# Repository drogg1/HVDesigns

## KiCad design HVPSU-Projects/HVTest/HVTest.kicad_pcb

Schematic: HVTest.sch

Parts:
J6, J7, J8: AWG_14_Hole; MountingHole_3.5mm_Pad

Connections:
GND: J6.1, J7.1, J8.1; also elsewhere on the board

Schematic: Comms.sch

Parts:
C1: 1u; R_0603
C2: 1u; C_0603
C3, C20: 0.1u; C_0402
D1, D2: LED; LED_0805
J1: USB-MICRO-B; USB-uB-Molex-1050170001-V2
P19: CONN_01X02; Pin_Header_Straight_SMT_02x01D
R1, R2: 1k; R_0805
R57: 1M; R_0402
U1: NUF2101MT1G; TSOP-6
U2: FT230X; QFN-16-1EP_4x4mm_Pitch0.65mm
Z1, Z2: MI0805K400R-10; L0805

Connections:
+5V: C2.1, C3.1, U2.10, Z2.1; also elsewhere on the board
/Comms/RXD: P19.2, U2.2; also elsewhere on the board
/Comms/TXD: P19.1, U2.15; also elsewhere on the board
/Comms/VCCIO: C1.1, R1.1, R2.1, U2.1, U2.8, U2.9
GND: C1.2, C2.2, C3.2, C20.2, R57.2, U2.3, U2.13, U2.17, Z1.1; also elsewhere on the board
GNDPWR: C20.1, J1.6, R57.1
unnamed: D1.1, U2.11
unnamed: D1.2, R1.2
unnamed: D2.1, U2.5
unnamed: D2.2, R2.2
unnamed: J1.1, U1.5, Z2.2
unnamed: J1.2, U1.4
unnamed: J1.3, U1.6
unnamed: J1.5, U1.2, Z1.2
unnamed: U1.1, U2.6
unnamed: U1.3, U2.7

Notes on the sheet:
VCCIO can supply a maximum of 50 mA.

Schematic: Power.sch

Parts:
BT1: Battery; KEY1027-ND
C6, C7: 1uF; C_0603
P1: CONN_01X02; Pin_Header_Straight_SMT_02x01D
P2, P3, P4: CONN_01X03; Pin_Header_Straight_1x03
P5, P6, P7: CONN_01X01; Pin_Header_Straight_1x01
S1: SPDT; PCM12SMTR
U4: MCP1700t-3302E/TT; SOT23

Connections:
+3V3: C7.1, P5.1, P6.1, P7.1, U4.3; also elsewhere on the board
+5V: C6.1, U4.2; also elsewhere on the board
GND: BT1.2, C6.2, C7.2, U4.1; also elsewhere on the board
unnamed: BT1.1, S1.2
unnamed: P1.2, S1.1
VBATT: P1.1, P2.1, P3.1, P4.1; also elsewhere on the board
VDAC: P2.3, P3.3, P4.3; also elsewhere on the board
VIC: P3.2; also elsewhere on the board
VREFDAC: P2.2; also elsewhere on the board
VSW: P4.2; also elsewhere on the board

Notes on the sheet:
Reference DAC Supply
Switch IC Supply
CW Chain Supply
250 mA LDO

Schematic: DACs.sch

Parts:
C8, C9: 0.1uF; C_0402
C81: 1uF; C_0603
U5: MAX5531; TQFN-12-1EP_4x4mm_Pitch0.8mmV2
U6: MCP4912; TSSOP-14_4.4x5mm_Pitch0.65mm
W1: TEST_1P; Measurement_Point_Round-SMD-Pad_Small

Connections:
+3V3: C8.1, U6.1, U6.9, U6.13; also elsewhere on the board
/CheetahSocket/MSPSCLK: U5.2, U6.4; also elsewhere on the board
/DACs/MOSI: U5.3, U6.5; also elsewhere on the board
/DACs/~REFCSN: U5.1; also elsewhere on the board
/DACs/~SUPPCSN: U6.3; also elsewhere on the board
DACO: U5.10, U5.12; also elsewhere on the board
GND: C8.2, C9.2, C81.2, U5.9, U5.EP, U6.8, U6.12; also elsewhere on the board
unnamed: U5.4, W1.1
VDAC: C81.1, U6.10; also elsewhere on the board
VHIGH: U6.14; also elsewhere on the board
VIC: U6.11; also elsewhere on the board
VREFDAC: C9.1, U5.8; also elsewhere on the board

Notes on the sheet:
ULP Reference DAC
Dual DAC to generate supply voltage as well as comparator high threshold
Selectable supply
3.3 V Supply current 0.25 mA (MCP4912)
Supply current 6 uA (MAX5531)

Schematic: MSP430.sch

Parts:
C4: 1uF; C_0603
C5, C80: 0.1uF; C_0402
D3: LED; LED_0805
P20: CONN_01X04; Pin_Header_Straight_SMT_04x01T
R3: 1k; R_0402
R13, R38: 4.7k; R_0402
R39: 1M; R_0402
R58, R59: 10k; R_0402
U3: MSP430G2XX3; TSSOP-28_4.4x9.7mm_Pitch0.65mm

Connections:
+3V3: C4.1, C5.1, P20.1, R13.2, R38.2, R39.1, R58.2, R59.2, U3.1; also elsewhere on the board
/CheetahSocket/MSPSCLK: U3.11; also elsewhere on the board
/CheetahSocket/~ICCSN: U3.13; also elsewhere on the board
/Comms/RXD: U3.4; also elsewhere on the board
/Comms/TXD: U3.3; also elsewhere on the board
/DACs/MOSI: U3.12; also elsewhere on the board
/DACs/~REFCSN: R59.1, U3.17; also elsewhere on the board
/DACs/~SUPPCSN: R58.1, U3.16; also elsewhere on the board
/HVMeasurement/SCL: R38.1, U3.22; also elsewhere on the board
/HVMeasurement/SDA: R13.1, U3.23; also elsewhere on the board
/MSP430/INTS0: U3.21; also elsewhere on the board
/MSP430/INTS1: U3.20; also elsewhere on the board
/MSP430/PWS0: U3.18; also elsewhere on the board
/MSP430/PWS1: U3.19; also elsewhere on the board
GND: C4.2, C5.2, C80.2, D3.1, P20.4, U3.28; also elsewhere on the board
LSB: U3.2; also elsewhere on the board
MSB: U3.5; also elsewhere on the board
unnamed: D3.2, R3.2
unnamed: P20.2, U3.25
unnamed: P20.3, R39.2, U3.24
unnamed: R3.1, U3.10
RSTIC: U3.15; also elsewhere on the board
SWCurr: C80.1, U3.6; also elsewhere on the board
VBATT: U3.7; also elsewhere on the board

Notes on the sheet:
Powered by 3V3 Regulator
Smoothing cap potenitally optional
Programming Header

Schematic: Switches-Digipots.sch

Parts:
C12, C17: 1nF; C_0402
C13: 3.3nF; C_0402
C14: 470pF; C_0402
C15, C16, C22: 0.1uF; C_0402
C18, C19: 220pF; C_0402
P9, P10, P11, P12: CONN_01X02; Pin_Header_Straight_SMT_02x01D
U8, U9: MAX4704; QFN-12-1EP_3x3mm_Pitch0.5mm
U10: MCP4651T; QFN-16-4x4

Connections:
+3V3: C15.1, C16.1, C22.1, U8.1, U9.1, U10.13, U10.14, U10.15, U10.16; also elsewhere on the board
/HVMeasurement/SCL: U10.1; also elsewhere on the board
/HVMeasurement/SDA: U10.2; also elsewhere on the board
/MSP430/INTS0: U9.10; also elsewhere on the board
/MSP430/INTS1: U9.9; also elsewhere on the board
/MSP430/PWS0: U8.10; also elsewhere on the board
/MSP430/PWS1: U8.9; also elsewhere on the board
/Switches-Digipots/INO0: C13.1, P10.2, U9.11
/Switches-Digipots/INO1: C17.1, U9.5
/Switches-Digipots/INO2: C19.1, U9.3
/Switches-Digipots/PNO0: C12.1, P9.2, U8.11
/Switches-Digipots/PNO1: C14.1, U8.5
/Switches-Digipots/PNO2: C18.1, U8.3
CIN: C12.2, C14.2, C18.2; also elsewhere on the board
GND: C15.2, C16.2, C22.2, U8.6, U8.7, U8.13, U9.6, U9.7, U9.13, U10.3, U10.4, U10.17; also elsewhere on the board
ICAP1: C13.2, C17.2, C19.2; also elsewhere on the board
ICAP2: P10.1, U9.12; also elsewhere on the board
P0W: P12.1, U10.9; also elsewhere on the board
P1W: P11.1, U10.6; also elsewhere on the board
RIN: P9.1, P12.2, U8.12, U10.10; also elsewhere on the board
SWITCH: P11.2, U10.5; also elsewhere on the board

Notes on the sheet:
Dual digipot for setting pulse width and delay resistances
Analog switch to select integration capacitor
Analog switch to select pulse width timing cap
Switch Bypass
Digipot Bypasses
I2C Address "0101A2A1A0" "0101111" <- Configured As
3.3 V Supply current 0.25 mA (MCP461T) 1 uA (MAX4704)

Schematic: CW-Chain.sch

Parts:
C23: 100uF; Tantalum_Case-C_EIA-6032-28_Reflow
C24, C30, C31, C33, C34, C38, C39, C41, C42, C46, C47, C49, C50, C54, C55, C57, C58, C62, C63, C65, C66, C70, C71, C73, C74: 0.1uF; C_1812
C25: 33pF; C_0402
C26: 3nF; C_0402
C27, C28, C29, C32, C35, C36, C37, C40, C43, C44, C45, C48, C51, C52, C53, C56, C59, C60, C61, C64, C67, C68, C69, C72: 0.1uF; C_1210
D4, D5, D6, D7, D8, D9, D10, D11, D12, D13, D14, D15: MMBD3004S; SOT23
GND1: CONN_01X01; Pin_Header_Straight_1x01
J2: SMA; SMA-EDGE
J3: UFL-CONN; U.FL-R-SMT
J4: RF_SHIELD_TWO_PIECES; BMI-S-230-F-R
OUT1: TEST_1P; Measurement_Point_Round-SMD-Pad_Small
P13: CONN_01X02; Pin_Header_Straight_SMT_02x01D
P17: CONN_01X01; Pin_Header_Straight_1x01
Q1: NMOS-DMG3420U; SOT23
R12: 5.1; R_0603
R14, R15: 1M; R_0402
R16, R17, R19, R20, R21, R22, R25, R26: 0; R_1206
R18, R23, R24, R27, R28, R29, R30, R31, R32, R33, R34, R35: 1M; R_0805
R36: 1G; R_2512
R37: 2M; R_0805
R52, R53: 0; R_0805
ST1, ST2, ST3, ST4, ST5, ST6, ST7, ST8, ST9, ST10, ST11, ST12: CONN_01X01; Pin_Header_Straight_1x01
U14: MAX9634; TSOT-23-5

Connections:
/CW-Chain/S1: C28.1, C30.1, C32.2, D4.3, D5.1, R16.1, R18.1, R19.2
/CW-Chain/S2: C32.1, C33.2, C36.2, D5.3, D6.1, R19.1, R21.2, R23.1
/CW-Chain/S3: C36.1, C38.1, C40.2, D6.3, D7.1, R21.1, R24.1, R25.2
/CW-Chain/S4: C40.1, C41.2, C44.2, D7.3, D8.1, R25.1, R27.1
GND: C23.2, C25.2, C28.2, C30.2, C31.2, C33.1, C34.1, C38.2, C39.2, C41.1, C42.1, C46.2, C47.2, C49.1, C50.1, C54.2, C55.2, C57.1, C58.1, C62.2, C63.2, C65.1, C66.1, C70.2, C71.2, C73.1, C74.1, D4.1, GND1.1, J2.2, J2.3, J2.4, J2.5, J3.2, J3.3, J4.1, Q1.3, R14.2, R15.2, R16.2, U14.1, U14.2; also elsewhere on the board
HVR: R36.2; also elsewhere on the board
unnamed 42: C23.1, R12.2, U14.4; also elsewhere on the board
unnamed: C24.2, C25.1, C26.1, OUT1.1, R15.1
unnamed: C26.2, J2.1, J3.1
unnamed 45: C27.1, R17.2; also elsewhere on the board
unnamed: C27.2, C29.1, D4.2, R17.1, R20.2
unnamed: C29.2, C35.1, D5.2, R20.1, R22.2
unnamed: C31.1, R18.2, ST1.1
unnamed: C34.2, R23.2, ST2.1
unnamed: C35.2, C37.1, D6.2, R22.1, R26.2
unnamed: C37.2, C43.1, D7.2, R26.1
unnamed: C39.1, R24.2, ST3.1
unnamed: C42.2, R27.2, ST4.1
unnamed: C43.2, C45.1, D8.2
unnamed: C44.1, C46.1, C48.2, D8.3, D9.1, R28.1
unnamed: C45.2, C51.1, D9.2
unnamed: C47.1, R28.2, ST5.1
unnamed: C48.1, C49.2, C52.2, D9.3, D10.1, R29.1
unnamed: C50.2, R29.2, ST6.1
unnamed: C51.2, C53.1, D10.2
unnamed: C52.1, C54.1, C56.2, D10.3, D11.1, R30.1
unnamed: C53.2, C59.1, D11.2
unnamed: C55.1, R30.2, ST7.1
unnamed: C56.1, C57.2, C60.2, D11.3, D12.1, R31.1
unnamed: C58.2, R31.2, ST8.1
unnamed: C59.2, C61.1, D12.2
unnamed: C60.1, C62.1, C64.2, D12.3, D13.1, R32.1
unnamed: C61.2, C67.1, D13.2
unnamed: C63.1, R32.2, ST9.1
unnamed: C64.1, C65.2, C68.2, D13.3, D14.1, R33.1
unnamed: C66.2, R33.2, ST10.1
unnamed: C67.2, C69.1, D14.2
unnamed: C68.1, C70.1, C72.2, D14.3, D15.1, R34.1
unnamed: C69.2, D15.2
unnamed: C71.1, R34.2, ST11.1
unnamed: C72.1, C73.2, D15.3, R35.1, R52.2
unnamed: C74.2, P17.1, R35.2, R37.2, R53.2
unnamed: P13.1, Q1.1, R14.1
unnamed 119: Q1.2; also elsewhere on the board
unnamed: R36.1, R52.1, R53.1
ST12: C24.1, R37.1, ST12.1
SWCurr: U14.3; also elsewhere on the board
SWDLY: P13.2; also elsewhere on the board
VSW: R12.1, U14.5; also elsewhere on the board

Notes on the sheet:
Populate to short out lower stages
Current Sense Amp
Optional
Feedback Res
Output

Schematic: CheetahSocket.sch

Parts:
J5: HIROSE-DF12; CheetahSocket
P14: CONN_01X03; Pin_Header_Straight_1x03_Pitch2.54mm
P23, P24: CONN_01X01; Pin_Header_Straight_1x01
P25: CONN_01X02; Pin_Header_Straight_1x02_Pitch2.54mm
R40, R41, R42: 10k; R_0402
R43, R44, R45: 1k; R_0402
U11: TLP293-4; SO-16-N

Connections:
+3V3: P25.1; also elsewhere on the board
/CheetahSocket/MSPSCLK: J5.17, P14.3, U11.1; also elsewhere on the board
/CheetahSocket/SPI1_SSa: R40.2, U11.12; also elsewhere on the board
/CheetahSocket/~ICCSN: J5.21, P14.1, U11.5; also elsewhere on the board
/DACs/MOSI: J5.19, P14.2, U11.3; also elsewhere on the board
/SwitchIC/MOSI: R41.2, U11.14; also elsewhere on the board
/SwitchIC/SCLK: R42.2, U11.16; also elsewhere on the board
GND: J5.2, J5.4, J5.6, P23.1, P24.1, R43.2, R44.2, R45.2, U11.11, U11.13, U11.15; also elsewhere on the board
unnamed: J5.1, J5.3, J5.5, P25.2
unnamed: R43.1, U11.6
unnamed: R44.1, U11.4
unnamed: R45.1, U11.2
VIC: R40.1, R41.1, R42.1; also elsewhere on the board

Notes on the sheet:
Opto-isolation
Potential connection to GPIO
Connector to MCA10 Optional connections to 3.3V supply
Currently outputs are buffered to decrease rise time to enable consistent SPI communication

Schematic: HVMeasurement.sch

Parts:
C75, C78, C79: 0.1uF; R_0402
C76, C77: 1uF; R_0603
P15: CONN_01X02; Pin_Header_Straight_SMT_02x01D
P18: CONN_01X01; Pin_Header_Straight_1x01
R48: 10M; R_0402
R49: 10k; R_0402
R50: 220k; R_0402
R51: 1k; R_0402
U12: LTC2050; TSOT-23-5
U13: LTC2451; DFN-8-1EP_2x3mm_Pitch0.5mm

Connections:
+3V3: C75.1, C76.1, C77.1, C79.1, U12.5, U13.3, U13.4; also elsewhere on the board
/HVMeasurement/SCL: U13.7; also elsewhere on the board
/HVMeasurement/SDA: U13.8; also elsewhere on the board
GND: C75.2, C76.2, C77.2, C78.2, C79.2, P15.2, R48.2, R49.1, U12.2, U13.1, U13.2, U13.5, U13.9; also elsewhere on the board
unnamed: C78.1, P15.1, R51.1, U13.6
unnamed: P18.1, R48.1, U12.3
unnamed: R49.2, R50.2, U12.4
unnamed: R50.1, R51.2, U12.1

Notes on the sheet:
128 mV @ 1206V worse case 1% tolerances
Av = 23 => 23*128 mV = 2.944 FS
12.7 nA @ 1206 V = 15.3 uW 6.3 nA @ 600 V = 3.78 uW worse case 1% tolerances
I2C Address "0010100"
3.3 V supply current 0.8 mA (LTC2050) 0.4 mA (LTC2451)
Connect 100G Res
Allows measurement of final HV stage with minimal loading (1000V/100Gohm = 10 nA => 10 uW)

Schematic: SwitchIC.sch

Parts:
C10, C11, C21: 1uF; C_0603
P8: CONN_01X02; Pin_Header_Straight_SMT_02x01V
P16, P22: CONN_01X02; Pin_Header_Straight_1x02_Pitch2.54mm
P21: CONN_01X03; Pin_Header_Straight_SMT_03x01STAGGERED
R4, R5: 10; R_0402
R6, R7, R8, R10, R11, R56: 1M; R_0402
R9: 33M; R_0402
R54: 560k; R_0402
R55: 2M; R_0402
RST1: TEST_1P; Pin_Header_Straight_SMT_01x01
RV1, RV2: 20k; EVM3Y-POT
RV3: 1M; EVM3Y-POT
U7: switch_ic4/5; test_socket

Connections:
/CheetahSocket/SPI1_SSa: U7.20; also elsewhere on the board
/SwitchIC/MOSI: U7.19; also elsewhere on the board
/SwitchIC/SCLK: U7.18; also elsewhere on the board
/SwitchIC/VDD: C11.1, R4.2, RV2.3, U7.15
/SwitchIC/VDDA: C10.1, R5.2, U7.11
CIN: U7.17; also elsewhere on the board
DACO: P8.2; also elsewhere on the board
GND: C10.2, C11.2, C21.2, R55.2, R56.1, U7.1, U7.12; also elsewhere on the board
HVR: P22.2, R6.2, R7.1, U7.3; also elsewhere on the board
ICAP1: U7.7; also elsewhere on the board
ICAP2: U7.8; also elsewhere on the board
LSB: P16.1, R9.1, U7.9; also elsewhere on the board
MSB: P16.2, R10.1, U7.10; also elsewhere on the board
unnamed: C21.1, P21.2, U7.2
unnamed: P8.1, R6.1
unnamed: P21.3, RV3.2
unnamed: P22.1, R9.2, R10.2
unnamed: R7.2, R8.2, U7.4
unnamed: R8.1, R11.1, U7.6
unnamed: R11.2, U7.5
unnamed: R54.2, RV3.1
unnamed: R55.1, RV3.3
P0W: RV2.2; also elsewhere on the board
P1W: RV1.2; also elsewhere on the board
RIN: U7.14; also elsewhere on the board
RSTIC: R56.2, RST1.1, U7.13; also elsewhere on the board
SWDLY: RV1.3; also elsewhere on the board
SWITCH: U7.16; also elsewhere on the board
VHIGH: P21.1; also elsewhere on the board
VIC: R4.1, R5.1, R54.1; also elsewhere on the board

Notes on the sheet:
Connects to 50k digipot Channel 0
Connects to array of switchable capacitors
Connects to 50k digipot Channel 1
Set reference current Iset = VDAC / R VsetHIGH = Iset * RFB = Iset * 1e9
ULP Ref DAC
Comparator High Threshold
Limits set point to ensure internal FETs stay in saturation
Sets R that, along with capacitor connected to CIN, sets pulse width of switching pulse
Controls rise and fall time of switch pulse

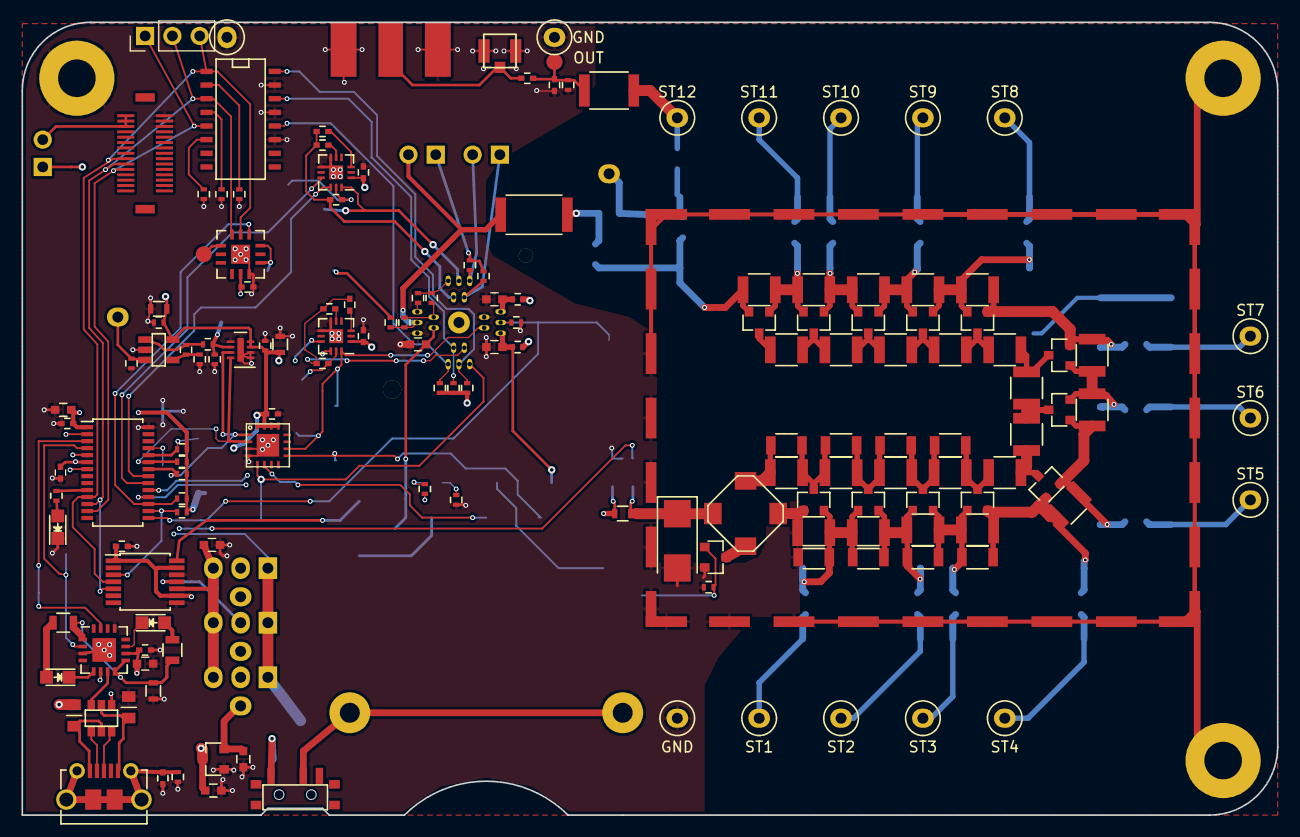
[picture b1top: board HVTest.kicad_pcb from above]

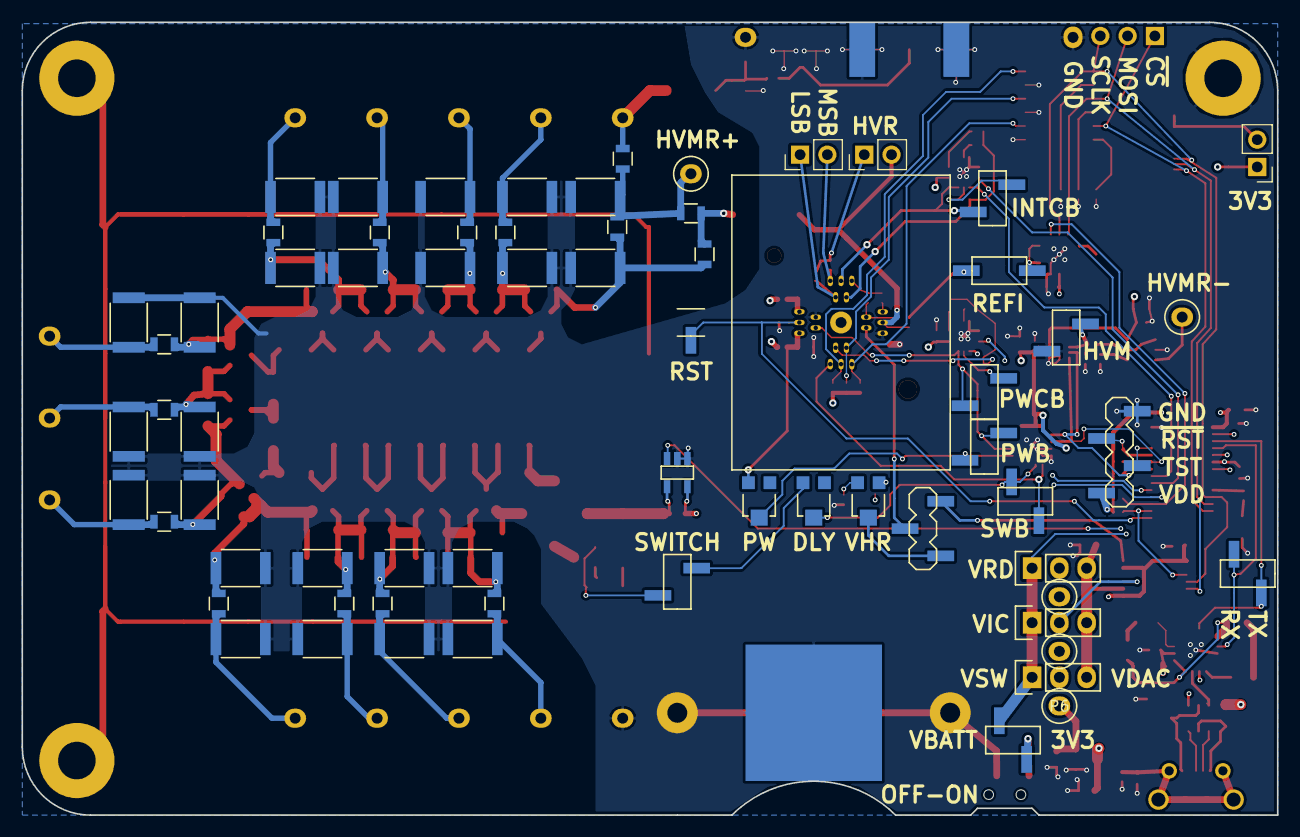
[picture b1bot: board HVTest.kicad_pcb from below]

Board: 4 copper layers, 116.8 x 73.8 mm, 225 parts (68 on the bottom side), 127 nets.

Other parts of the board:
T1: TRANSFO; LPR6235

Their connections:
GND: T1.3; also elsewhere on the board
unnamed 42: T1.1; also elsewhere on the board
unnamed 45: T1.4; also elsewhere on the board
unnamed 119: T1.2; also elsewhere on the board

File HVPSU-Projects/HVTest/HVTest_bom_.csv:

Component,Description,Part,References,Value,Footprint,Quantity Per PCB,Datasheet
1,Multiple-cell battery,Battery,BT1,Battery,KEY1027-ND,1,
2,Unpolarized capacitor,C,C3 C5 C8 C9 C15 C16 C20 C22 C80,0.1u,C_0402,9,
3,Unpolarized capacitor,C,C24 C30 C31 C33 C34 C38 C39 C41 C42 C46 C47 C49 C50 C54 C55 C57 C58 C62 C63 C65 C66 C70 C71 C73 C74,0.1uF,C_1812,25,
4,Unpolarized capacitor,C,C27 C28 C29 C32 C35 C36 C37 C40 C43 C44 C45 C48 C51 C52 C53 C56 C59 C60 C61 C64 C67 C68 C69 C72,0.1uF,C_1210,24,
5,Unpolarized capacitor,C,C75 C78 C79,0.1uF,R_0402,3,
6,"Polarized capacitor, US symbol",CP1,C23,100uF,Tantalum_Case-C_EIA-6032-28_Reflow,1,
7,Unpolarized capacitor,C,C12 C17,1nF,C_0402,2,
8,Unpolarized capacitor,C,C1 C76 C77,1u,R_0603,3,
9,Unpolarized capacitor,C,C2 C4 C6 C7 C10 C11 C21 C81,1u,C_0603,8,
10,Unpolarized capacitor,C,C18 C19,220pF,C_0402,2,
11,Unpolarized capacitor,C,C13,3.3nF,C_0402,1,
12,Unpolarized capacitor,C,C25,33pF,C_0402,1,
13,Unpolarized capacitor,C,C26,3nF,C_0402,1,
14,Unpolarized capacitor,C,C14,470pF,C_0402,1,
15,Light emitting diode,LED,D1 D2 D3,LED,LED_0805,3,
16,,MMBD3004S,D4 D5 D6 D7 D8 D9 D10 D11 D12 D13 D14 D15,MMBD3004S,SOT23,12,
17,,CONN_01X01-conn,GND1 P5 P6 P7 P17 P18 P23 P24 ST1 ST2 ST3 ST4 ST5 ST6 ST7 ST8 ST9 ST10 ST11 ST12,CONN_01X01,Pin_Header_Straight_1x01,20,
18,,HIROSE-DF12,J5,HIROSE-DF12,CheetahSocket,1,
19,Two-Piece EMI RF Shielding Cabinet,RF_SHIELD_TWO_PIECES,J4,RF_SHIELD_TWO_PIECES,BMI-S-230-F-R,1,
20,,SMA,J2,SMA,SMA-EDGE,1,
21,,UFL-CONN,J3,UFL-CONN,U.FL-R-SMT,1,
22,,USB-MICRO-B,J1,USB-MICRO-B,USB-uB-Molex-1050170001-V2,1,
23,,TEST_1P-conn,OUT1 W1,TEST_1P,Measurement_Point_Round-SMD-Pad_Small,2,
24,,CONN_01X02-conn,P1 P9 P10 P11 P12 P13 P15 P19,CONN_01X02,Pin_Header_Straight_SMT_02x01D,8,
25,,CONN_01X02-conn,P16 P22 P25,CONN_01X02,Pin_Header_Straight_1x02_Pitch2.54mm,3,
26,,CONN_01X02-conn,P8,CONN_01X02,Pin_Header_Straight_SMT_02x01V,1,
27,,CONN_01X03-conn,P14,CONN_01X03,Pin_Header_Straight_1x03_Pitch2.54mm,1,
28,,CONN_01X03-conn,P2 P3 P4,CONN_01X03,Pin_Header_Straight_1x03,3,
29,,CONN_01X03-conn,P21,CONN_01X03,Pin_Header_Straight_SMT_03x01STAGGERED,1,
30,,CONN_01X04-conn,P20,CONN_01X04,Pin_Header_Straight_SMT_04x01T,1,
31,,NMOS-DMG3420U,Q1,NMOS-DMG3420U,SOT23,1,
32,Resistor,R,R16 R17 R19 R20 R21 R22 R25 R26,0,R_1206,8,
33,Resistor,R,R52 R53,0,R_0805,2,
34,Resistor,R,R4 R5,10,R_0402,2,
35,Resistor,R,R48,10M,R_0402,1,
36,Resistor,R,R40 R41 R42 R49 R58 R59,10k,R_0402,6,
37,Resistor,R,R36,1G,R_2512,1,
38,Resistor,R,R6 R7 R8 R10 R11 R14 R15 R39 R56 R57,1M,R_0402,10,
39,Resistor,R,R18 R23 R24 R27 R28 R29 R30 R31 R32 R33 R34 R35,1M,R_0805,12,
40,Resistor,R,R1 R2,1k,R_0805,2,
41,Resistor,R,R3 R43 R44 R45 R51,1k,R_0402,5,
42,Resistor,R,R50,220k,R_0402,1,
43,Resistor,R,R37,2M,R_0805,1,
44,Resistor,R,R55,2M,R_0402,1,
45,Resistor,R,R9,33M,R_0402,1,
46,Resistor,R,R13 R38,4.7k,R_0402,2,
47,Resistor,R,R12,5.1,R_0603,1,
48,Resistor,R,R54,560k,R_0402,1,
49,,TEST_1P-conn,RST1,TEST_1P,Pin_Header_Straight_SMT_01x01,1,
50,,POT-RESCUE-HVTest,RV3,1M,EVM3Y-POT,1,
51,,POT-RESCUE-HVTest,RV1 RV2,20k,EVM3Y-POT,2,
52,,SPDT,S1,SPDT,PCM12SMTR,1,
53,,TRANSF1,TR1,TRANSF1,,1,
54,,FT230X,U2,FT230X,QFN-16-1EP_4x4mm_Pitch0.65mm,1,
55,,LTC2050,U12,LTC2050,TSOT-23-5,1,
56,,LTC2451,U13,LTC2451,DFN-8-1EP_2x3mm_Pitch0.5mm,1,
57,,MAX4704,U8 U9,MAX4704,QFN-12-1EP_3x3mm_Pitch0.5mm,2,
58,,MAX5531,U5,MAX5531,TQFN-12-1EP_4x4mm_Pitch0.8mmV2,1,
59,,MAX9634,U14,MAX9634,TSOT-23-5,1,
60,,MCP1700t-3302E_TT,U4,MCP1700t-3302E/TT,SOT23,1,
61,,MCP4651T,U10,MCP4651T,QFN-16-4x4,1,
62,,MCP4912,U6,MCP4912,TSSOP-14_4.4x5mm_Pitch0.65mm,1,
63,,MSP430G2XX3,U3,MSP430G2XX3,TSSOP-28_4.4x9.7mm_Pitch0.65mm,1,
64,,NUF2101MT1G,U1,NUF2101MT1G,TSOP-6,1,
65,,TLP293-4,U11,TLP293-4,SO-16-N,1,
66,,switch_ic4_5,U7,switch_ic4/5,test_socket,1,
67,,MI0805K400R-10,Z1 Z2,MI0805K400R-10,L0805,2,





Component Groups:,67
Component Count:,222
Fitted Components:,222
Number of PCBs:,1
Total components:,222
Schematic Version:,
Schematic Date:,
BoM Date:,2/6/2019 12:41:56 AM
Schematic Source:,C:\Users\User\Google Drive\IC Research\Clean HV Designs\HVPSU-Projects\HVTest\HVTest.sch
KiCad Version:,Eeschema (5.0.2)-1

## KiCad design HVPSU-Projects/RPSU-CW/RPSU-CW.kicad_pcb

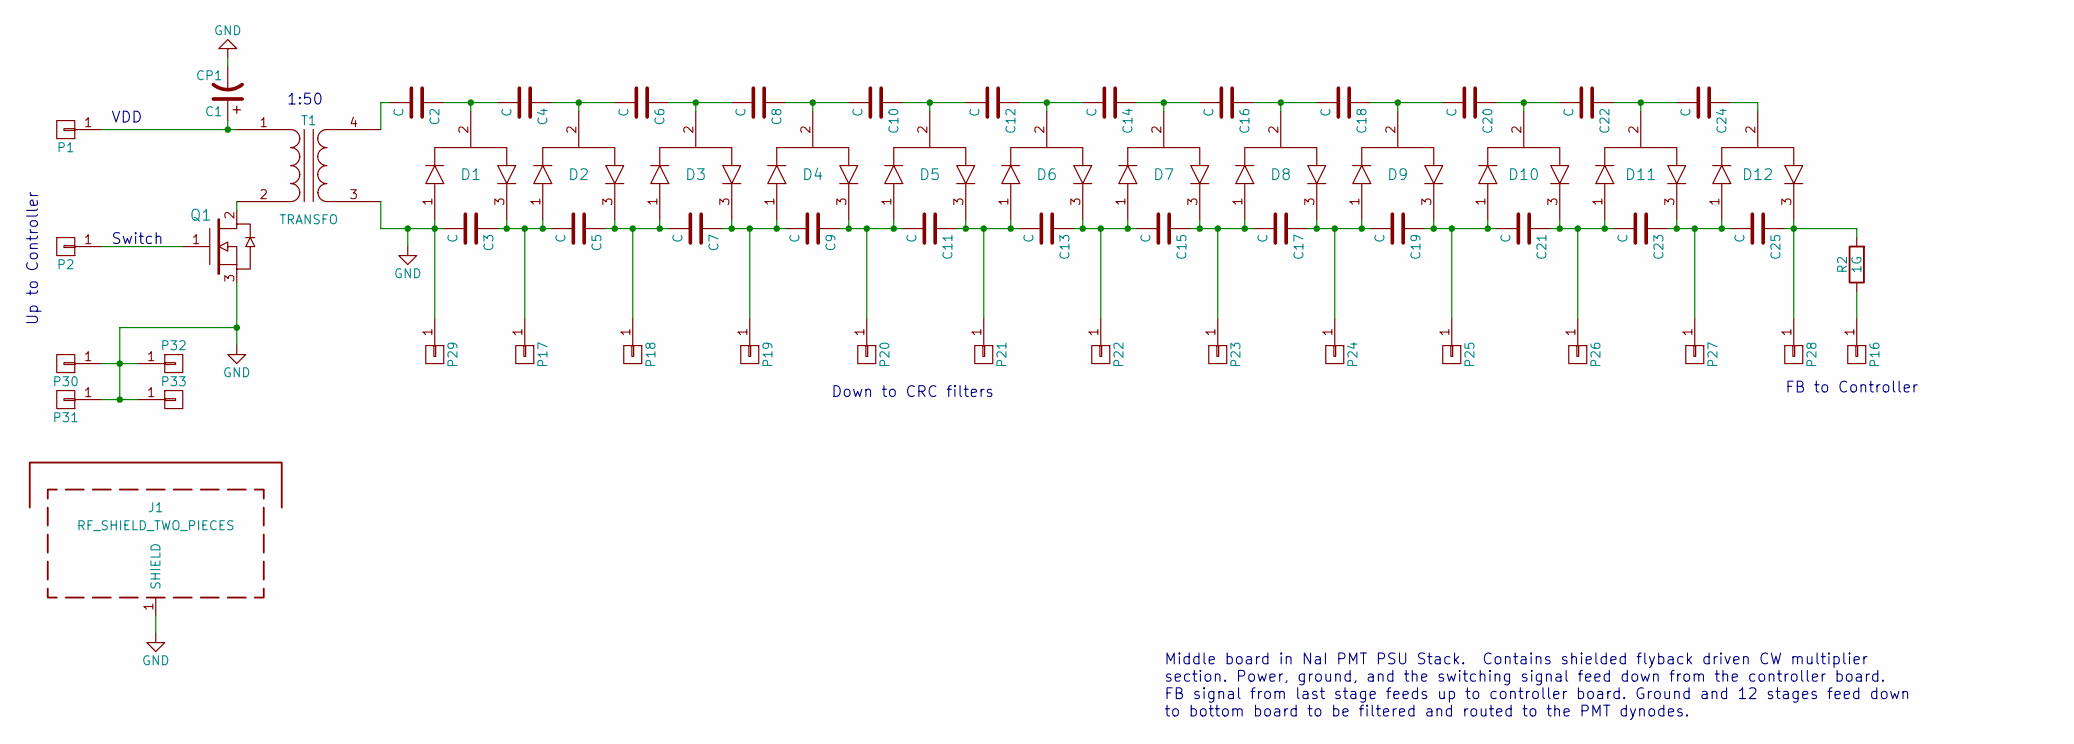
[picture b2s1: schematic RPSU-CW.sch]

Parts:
C1: CP1; CP_Tantalum_Case-C_EIA-6032-28_Reflow
C2, C3, C4, C5, C6, C7, C8, C9, C10, C11, C12, C13, C14, C15, C16, C17, C18, C19, C20, C21, C22, C23, C24, C25: C; HV-1206
D1, D2, D3, D4, D5, D6, D7, D8, D9, D10, D11, D12: MMBD3004S; SOT23
J1: RF_SHIELD_TWO_PIECES; Laird_Technologies_BMI-S-205-F_38.10x25.40mm
P1, P2, P16, P17, P18, P19, P20, P21, P23, P24, P25, P26, P27, P28, P29, P30, P31, P32, P33: CONN_01X01; PHS1x01_Pitch2.54mm_1D1.7P
P22: CONN_01X01; Pin_Header_Straight_SMT_01x01
Q1: NMOS-DMG3420U; SOT23
R2: 1G; R_2512
T1: TRANSFO; LPR6235

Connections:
GND: C1.2, C3.2, D1.1, J1.1, P29.1, P30.1, P31.1, P32.1, P33.1, Q1.3 (S), T1.3 (SA)
unnamed: C1.1, P1.1, T1.1 (AA)
unnamed: C2.1, C4.2, D1.2
unnamed: C2.2, T1.4 (SB)
unnamed: C3.1, C5.2, D1.3, D2.1, P17.1
unnamed: C4.1, C6.2, D2.2
unnamed: C5.1, C7.2, D2.3, D3.1, P18.1
unnamed: C6.1, C8.2, D3.2
unnamed: C7.1, C9.2, D3.3, D4.1, P19.1
unnamed: C10.1, C12.2, D5.2
unnamed: C8.1, C10.2, D4.2
unnamed: C11.1, C13.2, D5.3, D6.1, P21.1
unnamed: C9.1, C11.2, D4.3, D5.1, P20.1
unnamed: C12.1, C14.2, D6.2
unnamed: C13.1, C15.2, D6.3, D7.1, P22.1
unnamed: C14.1, C16.2, D7.2
unnamed: C15.1, C17.2, D7.3, D8.1, P23.1
unnamed: C16.1, C18.2, D8.2
unnamed: C17.1, C19.2, D8.3, D9.1, P24.1
unnamed: C18.1, C20.2, D9.2
unnamed: C19.1, C21.2, D9.3, D10.1, P25.1
unnamed: C20.1, C22.2, D10.2
unnamed: C21.1, C23.2, D10.3, D11.1, P26.1
unnamed: C22.1, C24.2, D11.2
unnamed: C23.1, C25.2, D11.3, D12.1, P27.1
unnamed: C24.1, D12.2
unnamed: C25.1, D12.3, P28.1, R2.2
unnamed: P2.1, Q1.1 (G)
unnamed: P16.1, R2.1
unnamed: Q1.2 (D), T1.2 (AB)

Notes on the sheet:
Up to Controller
Down to CRC filters
FB to Controller
1:50
Middle board in NaI PMT PSU Stack. Contains shielded flyback driven CW multiplier section. Power, ground, and the switching signal feed down from the controller board. FB signal from last stage feeds up to controller board. Ground and 12 stages feed down to bottom board to be filtered and routed to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
VDD
Switch

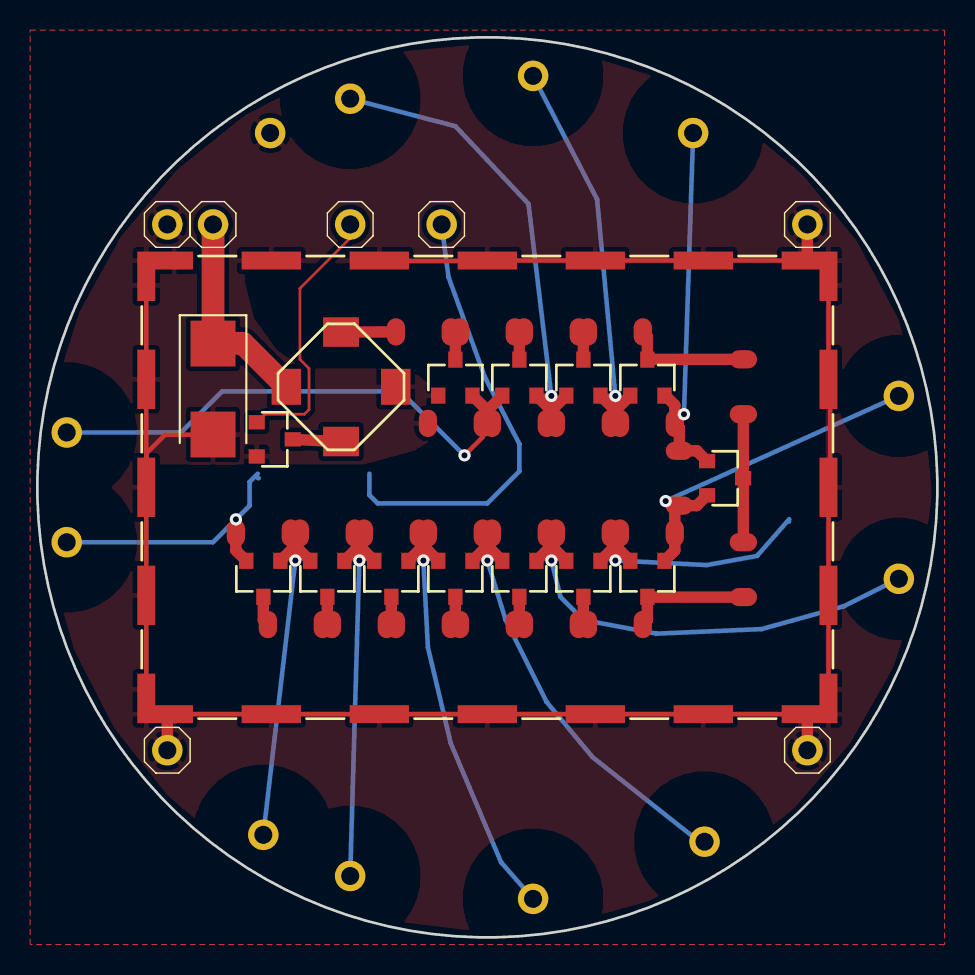
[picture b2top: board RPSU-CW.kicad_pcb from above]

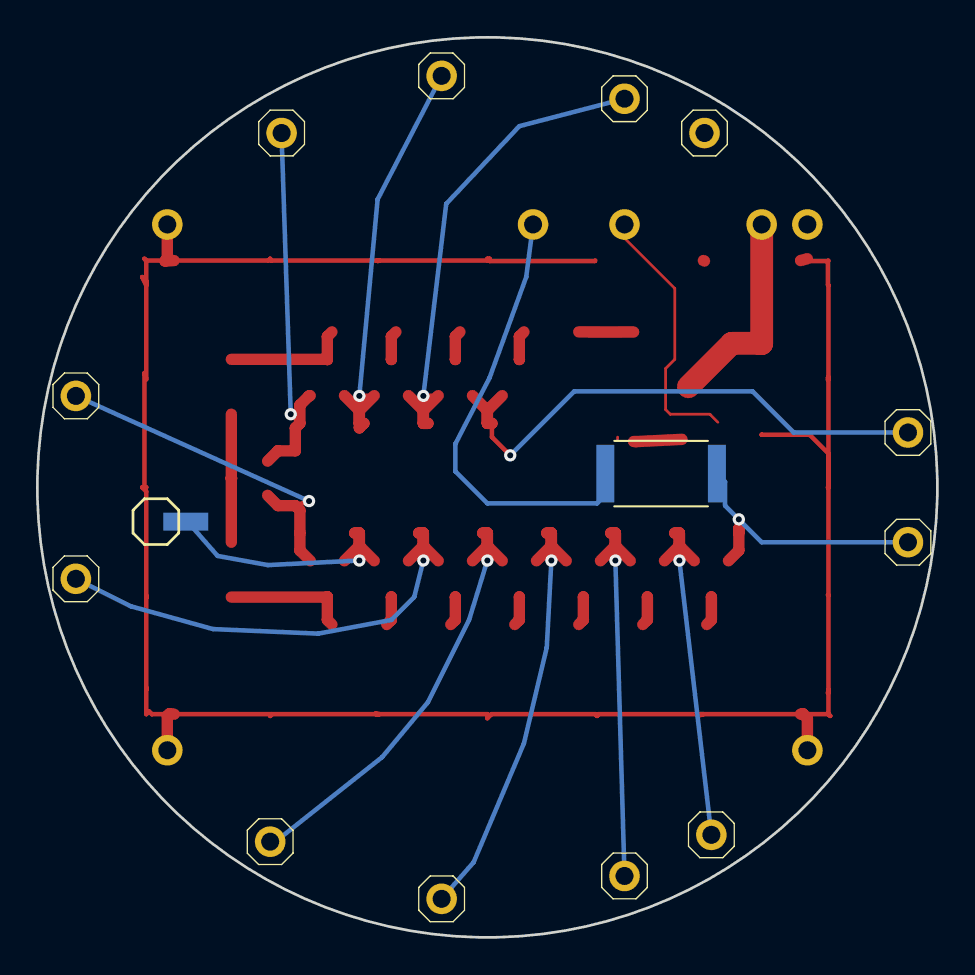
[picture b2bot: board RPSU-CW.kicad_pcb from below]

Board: 2 copper layers, 50.0 x 50.0 mm, 61 parts (14 on the bottom side), 30 nets.

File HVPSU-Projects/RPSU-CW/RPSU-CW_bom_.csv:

Component,Description,Part,References,Value,Footprint,Quantity Per PCB,Datasheet
1,Unpolarized capacitor,C,C2 C3 C4 C5 C6 C7 C8 C9 C10 C11 C12 C13 C14 C15 C16 C17 C18 C19 C20 C21 C22 C23 C24 C25,C,HV-1206,24,
2,Polarised capacitor,CP1,C1,CP1,CP_Tantalum_Case-C_EIA-6032-28_Reflow,1,
3,,MMBD3004S,D1 D2 D3 D4 D5 D6 D7 D8 D9 D10 D11 D12,MMBD3004S,SOT23,12,
4,,RF_SHIELD_TWO_PIECES,J1,RF_SHIELD_TWO_PIECES,Laird_Technologies_BMI-S-205-F_38.10x25.40mm,1,
5,Connector 01x01,CONN_01X01,P1 P2 P16 P17 P18 P19 P20 P21 P23 P24 P25 P26 P27 P28 P29 P30 P31 P32 P33,CONN_01X01,PHS1x01_Pitch2.54mm_1D1.7P,19,
6,Connector 01x01,CONN_01X01,P22,CONN_01X01,Pin_Header_Straight_SMT_01x01,1,
7,,NMOS-DMG3420U,Q1,NMOS-DMG3420U,SOT23,1,
8,Resistor,R,R2,1G,R_2512,1,
9,,TRANSFO,T1,TRANSFO,LPR6235,1,
,,,,,,,
,,,,,,,
,,,,,,,
,,,,,,,
,,,,,,,
Component Groups:,9,,,,,,
Component Count:,61,,,,,,
Fitted Components:,61,,,,,,
Number of PCBs:,1,,,,,,
Total components:,61,,,,,,
Schematic Version:,,,,,,,
Schematic Date:,,,,,,,
BoM Date:,1/29/2019 21:47,,,,,,
Schematic Source:,C:/Users/User/Google Drive/IC Research/Clean HV Designs/HVPSU-Projects/RPSU-CW/RPSU-CW.sch,,,,,,
KiCad Version:,Eeschema 4.0.2-stable,,,,,,

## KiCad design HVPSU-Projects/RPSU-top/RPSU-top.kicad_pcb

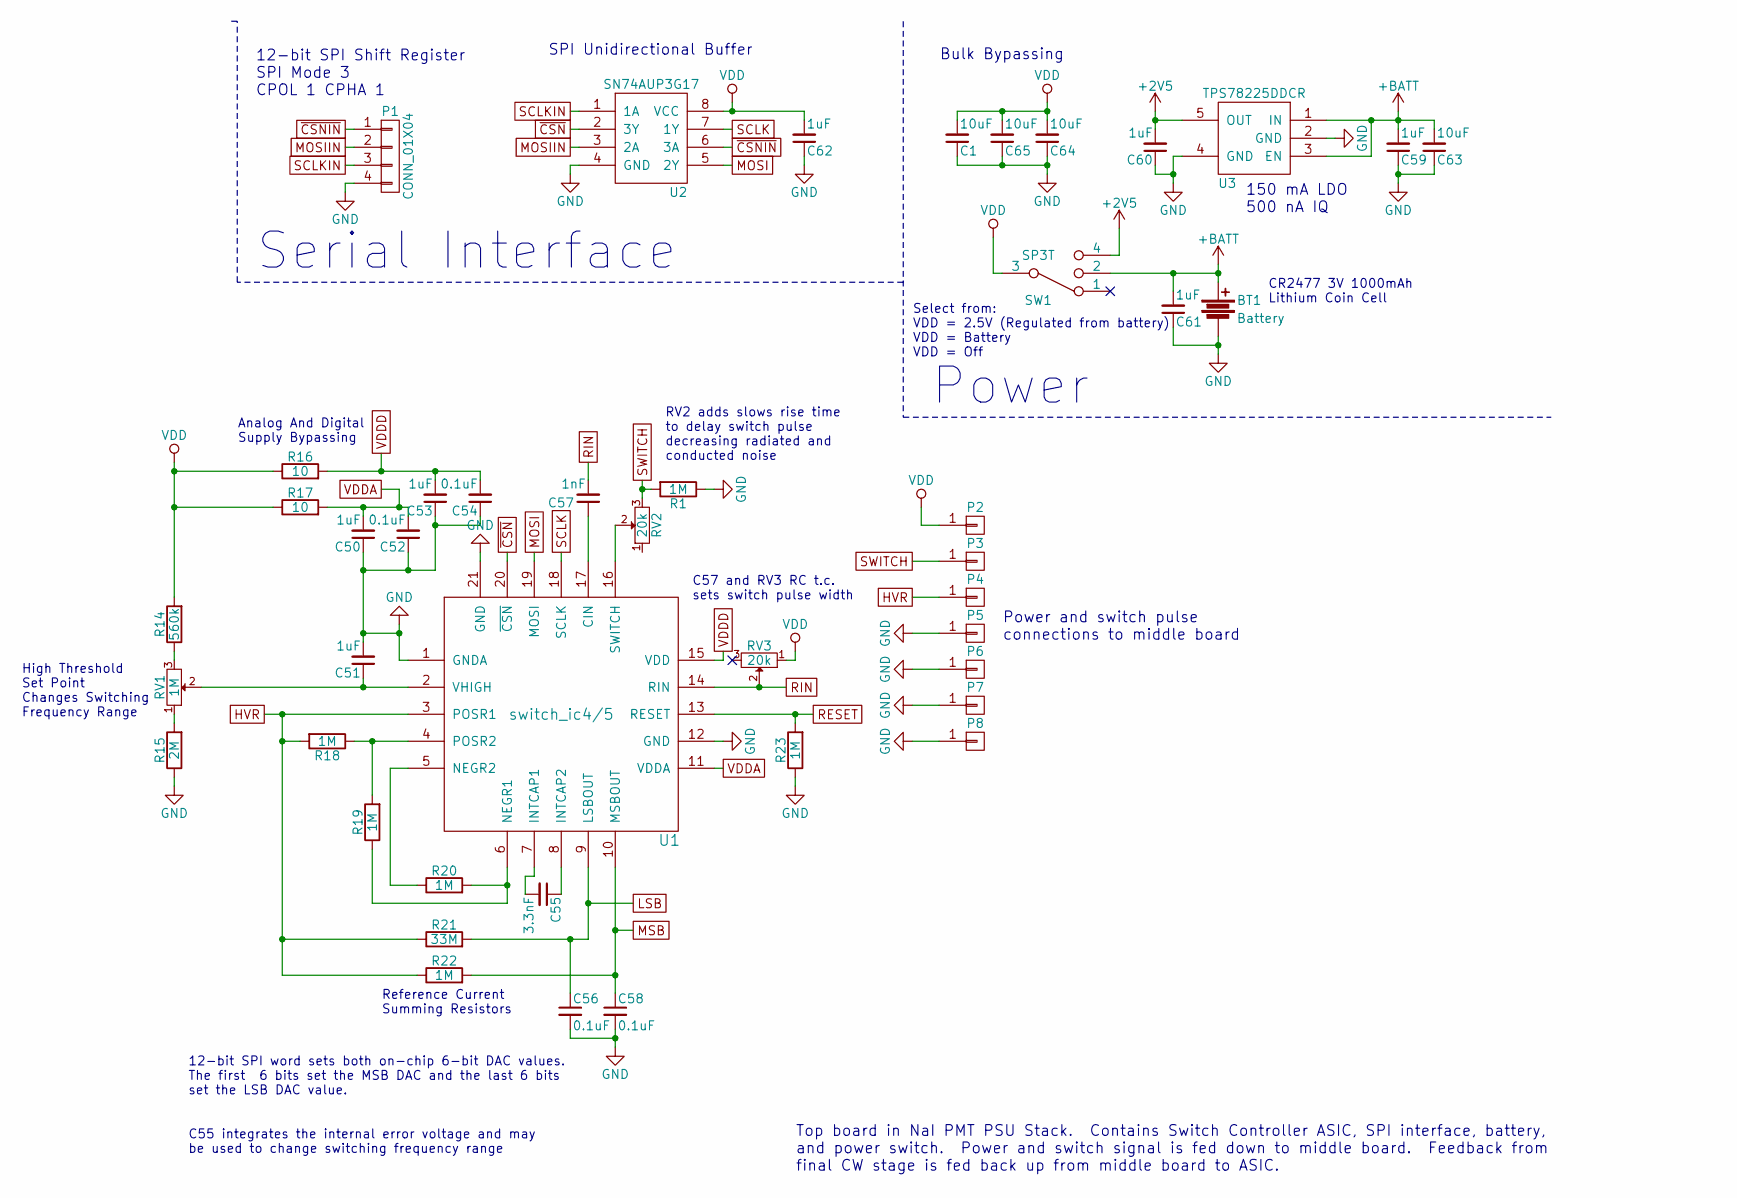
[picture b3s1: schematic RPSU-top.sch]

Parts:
BT1: Battery; KEY1027-ND-rev2
C1, C63, C64, C65: 10uF; C_1206
C50, C51, C53, C59, C60, C61, C62: 1uF; C_0603
C52, C54, C56, C58: 0.1uF; C_0402_NoSilk
C55: 3.3nF; C_0402_NoSilk
C57: 1nF; C_0402_NoSilk
P1: CONN_01X04; SM04B-SRSS-TB(LF)(SN)
P2, P3, P4, P5, P6, P7, P8: CONN_01X01; PHS1x01_Pitch2.54mm_1D1.7P
R1, R18, R19, R20, R22, R23: 1M; R_0402_NoSilk
R14: 560k; R_0402_NoSilk
R15: 2M; R_0402_NoSilk
R16, R17: 10; R_0402_NoSilk
R21: 33M; R_0402_NoSilk
RV1: 1M; EVM3Y-POT
RV2, RV3: 20k; EVM3Y-POT
SW1: SP3T; PCM13SMTR
U1: switch_ic4/5; QFN-20-1EP_4x4mm_Pitch0.5mm
U2: SN74AUP3G17; 8-VFSOP
U3: TPS78225DDCR; TSOT-23-5

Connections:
+2V5: C60.2, SW1.4, U3.5 (OUT)
+BATT: BT1.1, C59.2, C61.2, C63.2, SW1.2, U3.1 (IN), U3.3 (EN)
GND: BT1.2, C1.1, C50.1, C51.2, C52.1, C53.1, C54.1, C56.2, C58.2, C59.1, C60.1, C61.1, C62.1, C63.1, C64.1, C65.1, P1.4, P5.1, P6.1, P7.1, P8.1, R1.1, R15.1, R23.1, U1.1 (GNDA), U1.12 (GND), U1.21 (GND), U2.4 (GND), U3.2 (GND), U3.4 (GND)
HVR: P4.1, R18.2, R21.1, R22.1, U1.3 (POSR1)
LSB: C56.1, R21.2, U1.9 (LSBOUT)
MOSI: U1.19 (MOSI), U2.5 (2Y)
MOSIIN: P1.2, U2.3 (2A)
MSB: C58.1, R22.2, U1.10 (MSBOUT)
unnamed: C51.1, RV1.2, U1.2 (VHIGH)
unnamed: C55.1, U1.8 (INTCAP2)
unnamed: C55.2, U1.7 (INTCAP1)
unnamed: C57.1, U1.17 (CIN)
unnamed: R14.1, RV1.3
unnamed: R15.2, RV1.1
unnamed: R18.1, R19.2, U1.4 (POSR2)
unnamed: R19.1, R20.2, U1.6 (NEGR1)
unnamed: R20.1, U1.5 (NEGR2)
unnamed: RV2.2, U1.16 (SWITCH)
RESET: R23.2, U1.13 (RESET)
RIN: C57.2, RV3.2, U1.14 (RIN)
SCLK: U1.18 (SCLK), U2.7 (1Y)
SCLKIN: P1.3, U2.1 (1A)
SWITCH: P3.1, R1.2, RV2.3
VDD: C1.2, C62.2, C64.2, C65.2, P2.1, R14.2, R16.1, R17.1, RV3.1, SW1.3, U2.8 (VCC)
VDDA: C50.2, C52.2, R17.2, U1.11 (VDDA)
VDDD: C53.2, C54.2, R16.2, U1.15 (VDD)
~CSN: U1.20 (~CSN), U2.2 (3Y)
~CSNIN: P1.1, U2.6 (3A)

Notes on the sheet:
Power
Serial Interface
12-bit SPI Shift Register SPI Mode 3 CPOL 1 CPHA 1
SPI Unidirectional Buffer
150 mA LDO 500 nA IQ
Select from: VDD = 2.5V (Regulated from battery) VDD = Battery VDD = Off
Power and switch pulse connections to middle board
Bulk Bypassing
C57 and RV3 RC t.c. sets switch pulse width
RV2 adds slows rise time to delay switch pulse decreasing radiated and conducted noise
Analog And Digital Supply Bypassing
High Threshold Set Point Changes Switching Frequency Range
Reference Current Summing Resistors
12-bit SPI word sets both on-chip 6-bit DAC values. The first 6 bits set the MSB DAC and the last 6 bits set the LSB DAC value.
C55 integrates the internal error voltage and may be used to change switching frequency range
CR2477 3V 1000mAh Lithium Coin Cell
Top board in NaI PMT PSU Stack. Contains Switch Controller ASIC, SPI interface, battery, and power switch. Power and switch signal is fed down to middle board. Feedback from final CW stage is fed back up from middle board to ASIC.
